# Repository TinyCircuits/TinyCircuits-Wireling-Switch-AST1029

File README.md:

# TinyCircuits Wireling Switch
# AST1029 Rev1

The design files are located under design_files/ for the TinyCircuits AST1029 Rev 1 PCB. This is a Wirelingboard which features an on/off type slide switch.
NOTE: this board is used to output High/Low logic signals and not to make or break power.

Format is in Cadsoft Eagle format - Eagle version 6.2 was used for the original design.

For more infomation on this, check out the product page at TinyCircuits.com

# License:

Design by TinyCircuits.
All design files are released under the Creative Commons Attribution Share-Alike 3.0 License, see the following link for details: http://creativecommons.org/licenses/by-sa/3.0

All text above must be included in any redistribution or derived design

This project uses designs and concepts developed as part of the Arduino project and the LilyPad project.  The TinyCircuits design files themselves (schematics, PCB and libraries) are not directly derived from these works' design files and have been created new, however the concepts and basic architecture behind the TinyDuino and TinyLily products are derived and we thank the hard work of the organizations below for their contributions to open-source hardware:
  
Original Arduino Uno Design by Team Arduino

LilyPad Arduino Design by Leah Buechley and Sparkfun Electronics

Please support the open-source hardware community

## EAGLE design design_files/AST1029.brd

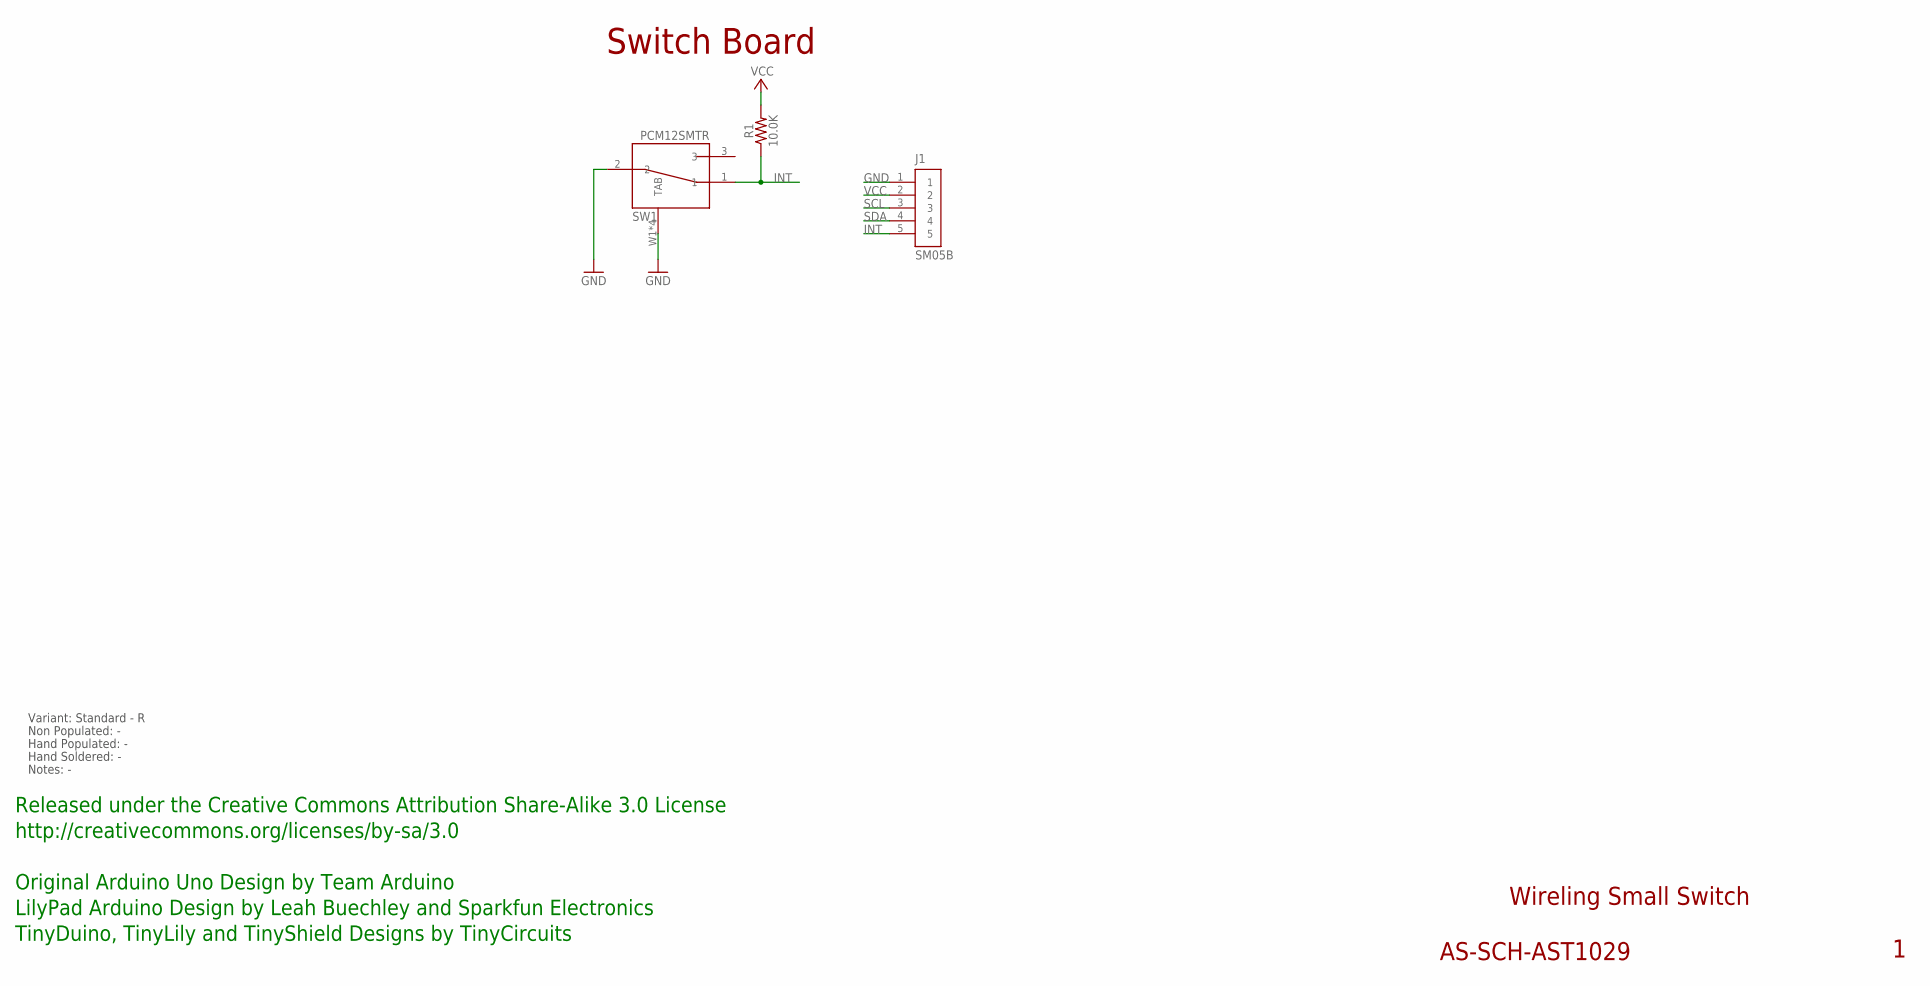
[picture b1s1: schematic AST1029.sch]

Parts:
J1: SM05B; JST_SH_5X1_EDGE
R1: 10.0K; 0402
SW1: PCM12SMTR

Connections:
GND: J1.1, SW1.2, SW1.W1 (TAB), SW1.W2 (TAB), SW1.W3 (TAB), SW1.W4 (TAB)
INT: J1.5, R1.1, SW1.1
SCL: J1.3
SDA: J1.4
VCC: J1.2, R1.2

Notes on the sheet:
Wireling Small Switch
AS-SCH-AST1029
Switch Board
Released under the Creative Commons Attribution Share-Alike 3.0 License
http://creativecommons.org/licenses/by-sa/3.0
Original Arduino Uno Design by Team Arduino
TinyDuino, TinyLily and TinyShield Designs by TinyCircuits
LilyPad Arduino Design by Leah Buechley and Sparkfun Electronics
Non Populated: -
Hand Populated: -
Hand Soldered: -
Notes: -
Variant: Standard - R

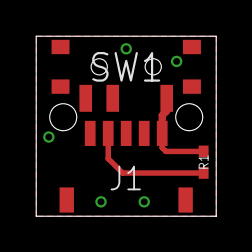
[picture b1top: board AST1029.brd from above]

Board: 2 copper layers, 10.0 x 10.0 mm, 4 parts (0 on the bottom side), 3 nets.

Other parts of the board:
U$1: DOCFIELD-TINYCIRCUITS-PCB

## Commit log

2019-07-30 added example sketch
2019-07-30 cleaned up code
2019-08-05 added datasheet
2019-10-29 updates:
2019-12-30 updated documentation
2020-02-04 mass image update
2020-08-14 Add CAD data
